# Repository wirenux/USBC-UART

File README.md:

# USB-C to UART Bridge

A simple project to convert a traditional USB-B UART bridge schematic to a modern **USB-C** interface.

---

## PCB & 3D

## CC Resistors

For the device to work with **USB-C to USB-C cables**, you must add two resistors to the configuration pins:

* **CC1 (Pin A5):** Connect a **5.1kΩ** resistor to **GND**.
* **CC2 (Pin B5):** Connect a **5.1kΩ** resistor to **GND**.

---

## Schematic

---

## License

This project is under [MIT](./LICENSE) license.

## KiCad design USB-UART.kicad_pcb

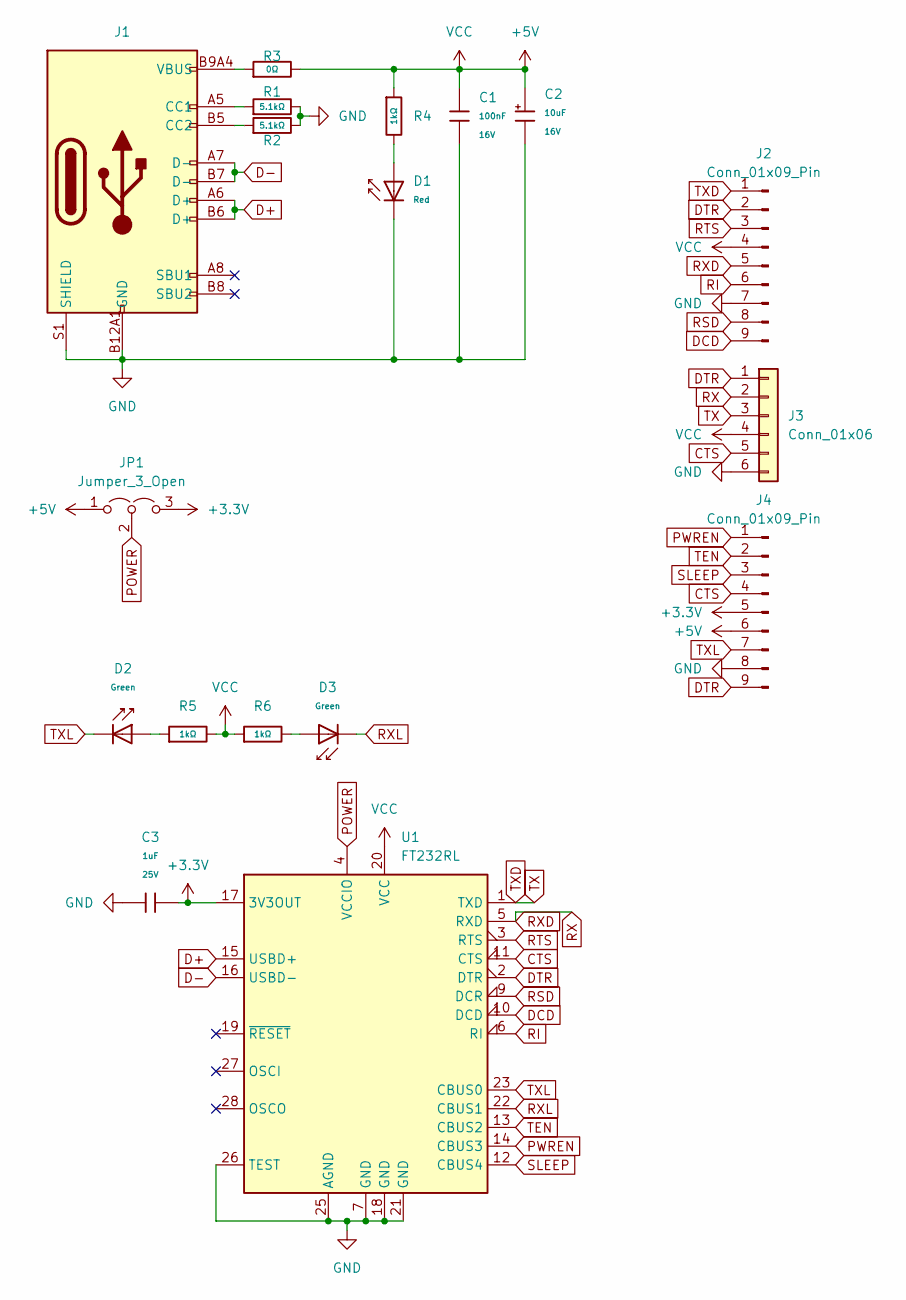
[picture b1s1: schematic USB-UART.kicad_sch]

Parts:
C1: 100nF; C_0402; Voltage Rated 16V; Tolerance ±10%; Part CL05B104KO5NNNC; LCSC C1525
C2: 10uF; C_CASE-A-3216-18(mm); Tolerance ±10%; Rated Voltage 16V; Part TAJA106K016RNJ; LCSC C7171
C3: 1uF; C_0402; Voltage Rated 25V; Tolerance ±10%; Part CL05A105KA5NQNC; LCSC C52923
D1: Red; D_0603; Part KT-0603R; LCSC C2286
D2, D3: Green; D_0805; Part KT-0805G; LCSC C2297
J1: Connector, USB-TYPE-C-16P; TYPE-C-SMD_HX-TYPE-C-16PIN; LCSC C2927039
J2, J4: Conn_01x09_Pin; PinHeader_1x09_P2.54mm_Vertical
J3: Conn_01x06; PinHeader_1x06_P2.54mm_Horizontal
JP1: Jumper_3_Open; PinHeader_1x03_P2.54mm_Vertical
R1, R2: 5.1kΩ; R_0603; Overload Voltage (Max) 75V; Tolerance ±1%; Part 0603WAF5101T5E; LCSC C23186
R3: 0Ω; R_0603; Overload Voltage (Max) 75V; Tolerance ±1%; Part 0603WAF0000T5E; LCSC C21189
R4, R5, R6: 1kΩ; R_0603; Overload Voltage (Max) 75V; Tolerance ±1%; Part 0603WAF1001T5E; LCSC C21190
U1: FT232RL; SSOP-28_5.3x10.2mm_P0.65mm

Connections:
+3.3V: C3.2, J4.5, JP1.3 (B), U1.17 (3V3OUT)
+5V: C1.1, C2.1, J2.4, J3.4, J4.6, JP1.1 (A), R3.2, R4.1, R5.2, R6.1, U1.20 (VCC)
CTS: J3.5, J4.4, U1.11 (CTS)
D+: J1.A6 (D+), J1.B6 (D+), U1.15 (USBD+)
D-: J1.A7 (D-), J1.B7 (D-), U1.16 (USBD-)
DCD: J2.9, U1.10 (DCD)
DTR: J2.2, J3.1, J4.9, U1.2 (DTR)
GND: C1.2, C2.2, C3.1, D1.1, J1.A12B1 (GND), J1.B12A1 (GND), J1.S1 (SHIELD), J2.7, J3.6, J4.8, R1.2, R2.2, U1.7 (GND), U1.18 (GND), U1.21 (GND), U1.25 (AGND), U1.26 (TEST)
unnamed: D1.2, R4.2
unnamed: D2.2, R5.1
unnamed: D3.2, R6.2
unnamed: J1.A5 (CC1), R1.1
unnamed: J1.B5 (CC2), R2.1
unnamed: J1.A9B4 (VBUS), J1.B9A4 (VBUS), R3.1
POWER: JP1.2 (C), U1.4 (VCCIO)
PWREN: J4.1, U1.14 (CBUS3)
RI: J2.6, U1.6 (RI)
RSD: J2.8, U1.9 (DCR)
RTS: J2.3, U1.3 (RTS)
RX: J2.5, J3.2, U1.5 (RXD)
RXL: D3.1, U1.22 (CBUS1)
SLEEP: J4.3, U1.12 (CBUS4)
TEN: J4.2, U1.13 (CBUS2)
TX: J2.1, J3.3, U1.1 (TXD)
TXL: D2.1, J4.7, U1.23 (CBUS0)

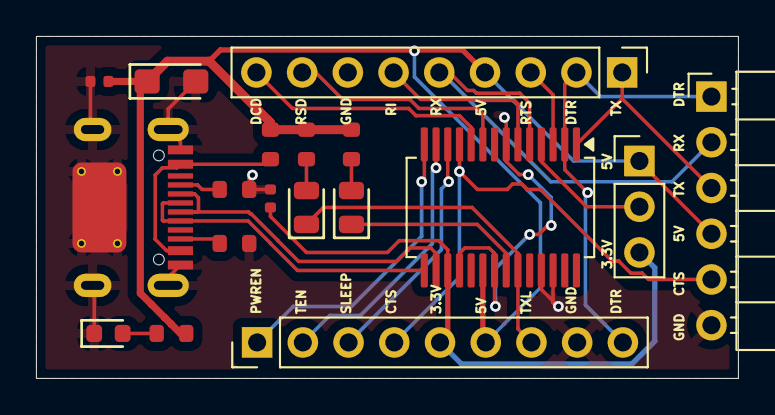
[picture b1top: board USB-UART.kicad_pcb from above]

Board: 2 copper layers, 39.0 x 19.0 mm, 18 parts (0 on the bottom side), 25 nets.

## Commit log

2026-03-31 init
2026-03-31 remove useless files
2026-03-31 add: github link
2026-03-31 add: README.md + LICENSE
2026-03-31 Fix formatting of License section in README
